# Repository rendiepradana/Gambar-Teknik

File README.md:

# Gambar-Teknik

Hello i'am Rendie Pradana

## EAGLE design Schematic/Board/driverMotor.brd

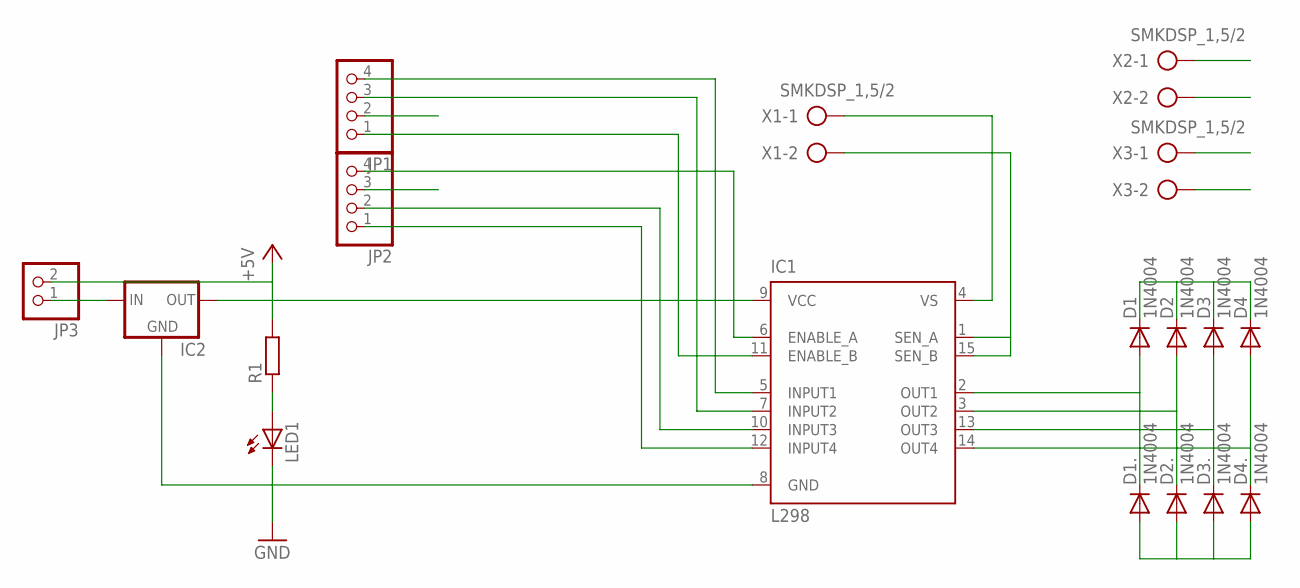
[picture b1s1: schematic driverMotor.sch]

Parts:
D1, D1., D2, D2., D3, D3., D4, D4.: 1N4004; DO41-10
IC1: L298; MULTIWATT-15
IC2: 78MXXS
JP1, JP2: PINHD-1X4; 1X04
JP3: PINHD-1X2; 1X02
LED1: LED5MM
R1: R-EU_0411/12; 0411/12
X1, X2, X3: SMKDSP_1,5/2

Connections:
+5V: IC1.9 (VCC), IC2.OUT, JP1.2, JP3.2, R1.2
ENABLE_A: IC1.6 (ENABLE_A), JP2.4
ENABLE_B: IC1.11 (ENABLE_B), JP1.1
GND: D1..A, D2..A, D3..A, D4..A, IC1.1 (SEN_A), IC1.8 (GND), IC1.15 (SEN_B), IC2.GND, JP2.3, LED1.K (C), X1.2
INPUT1: IC1.5 (INPUT1), JP1.4
INPUT2: IC1.7 (INPUT2), JP1.3
INPUT3: IC1.10 (INPUT3), JP2.2
INPUT4: IC1.12 (INPUT4), JP2.1
LED: LED1.A, R1.1
MOTOR1_1: D1.A, D1..C, IC1.2 (OUT1), X2.1
MOTOR1_2: D2.A, D2..C, IC1.3 (OUT2), X2.2
MOTOR2_1: D3.A, D3..C, IC1.13 (OUT3), X3.1
MOTOR2_2: D4.A, D4..C, IC1.14 (OUT4), X3.2
VS: D1.C, D2.C, D3.C, D4.C, IC1.4 (VS), IC2.IN, JP3.1, X1.1

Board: 2 copper layers, 18 parts (0 on the bottom side), 14 nets, no tracks yet.

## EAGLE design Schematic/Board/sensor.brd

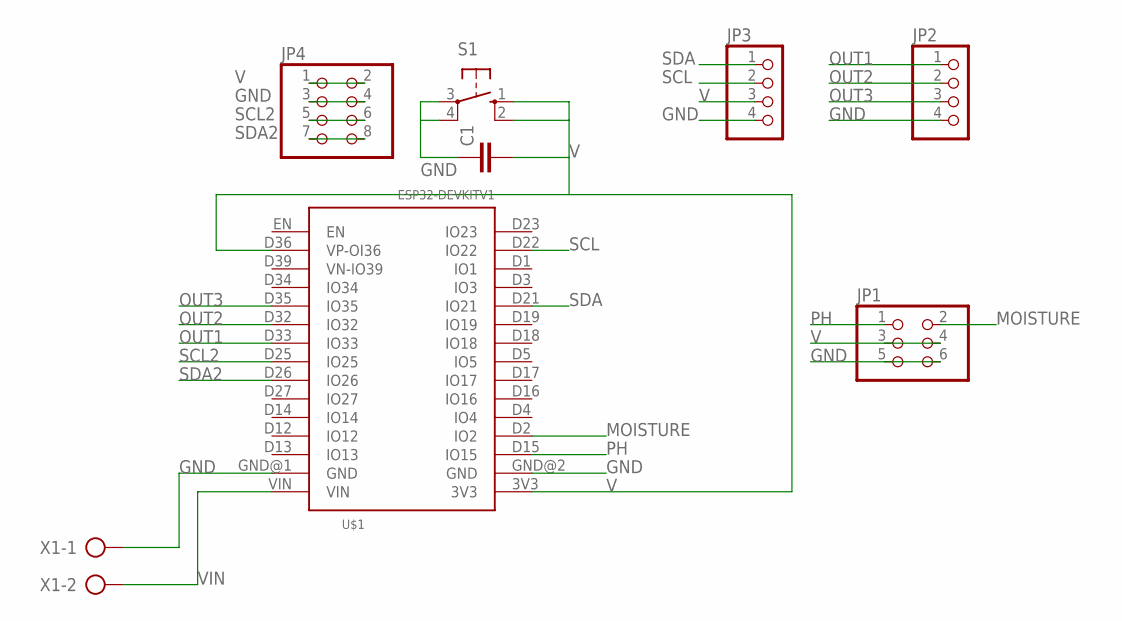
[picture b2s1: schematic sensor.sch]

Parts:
C1: C-EU050-030X075; C050-030X075
JP1: PINHD-2X3; 2X03
JP2, JP3: PINHD-1X4; 1X04
JP4: PINHD-2X4; 2X04
S1: 10-XX; B3F-10XX
U$1: ESP32DEVKITV1; ESP32-DEVKITV1
X1: AK300/2

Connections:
GND: C1.1, JP1.5, JP1.6, JP2.4, JP3.4, JP4.3, JP4.4, S1.3, S1.4 (P1), U$1.GND@1 (GND), U$1.GND@2 (GND), X1.1
MOISTURE: JP1.2, U$1.D2 (IO2)
OUT1: JP2.1, U$1.D33 (IO33)
OUT2: JP2.2, U$1.D32 (IO32)
OUT3: JP2.3, U$1.D35 (IO35)
PH: JP1.1, U$1.D15 (IO15)
SCL: JP3.2, U$1.D22 (IO22)
SCL2: JP4.5, JP4.6, U$1.D25 (IO25)
SDA: JP3.1, U$1.D21 (IO21)
SDA2: JP4.7, JP4.8, U$1.D26 (IO26)
V: C1.2, JP1.3, JP1.4, JP3.3, JP4.1, JP4.2, S1.1 (S), S1.2 (S1), U$1.3V3, U$1.D36 (VP-OI36)
VIN: U$1.VIN, X1.2

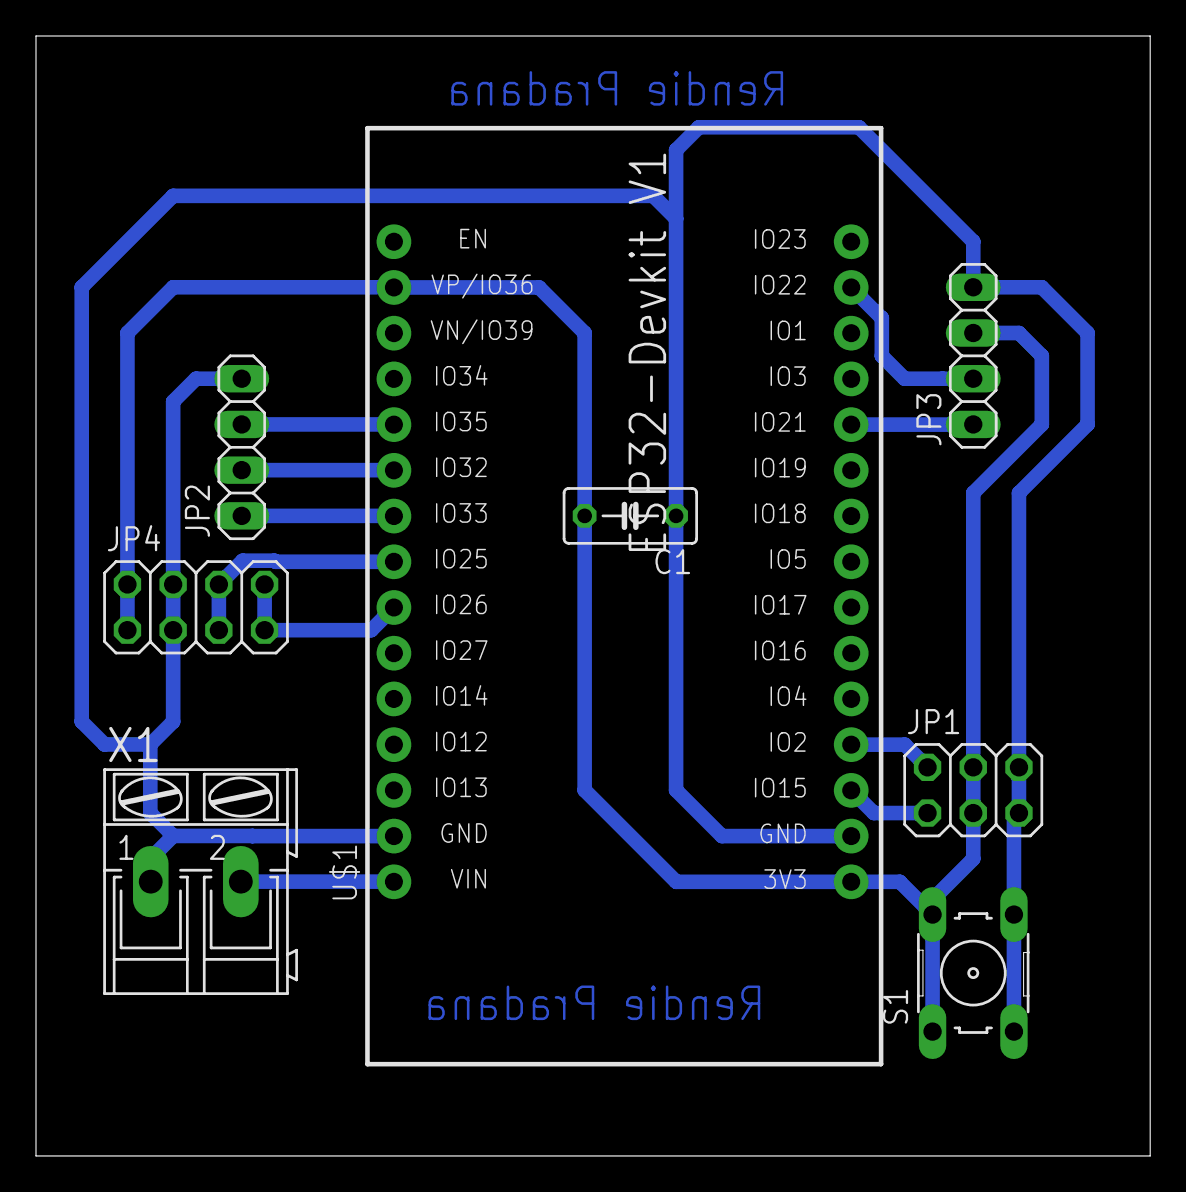
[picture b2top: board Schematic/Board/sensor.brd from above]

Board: 2 copper layers, 61.9 x 62.2 mm, 8 parts (0 on the bottom side), 12 nets.

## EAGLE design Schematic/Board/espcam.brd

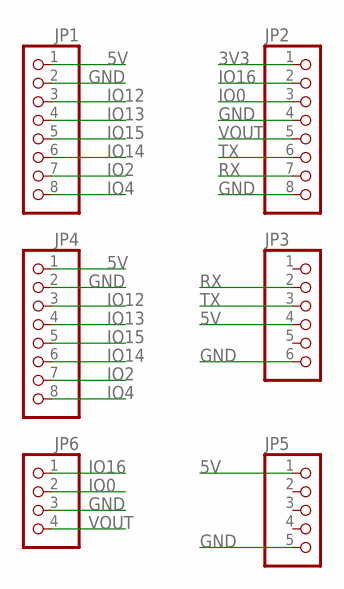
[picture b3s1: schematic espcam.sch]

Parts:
JP1, JP2, JP4: PINHD-1X8; 1X08
JP3: PINHD-1X6; 1X06
JP5: PINHD-1X5; 1X05
JP6: PINHD-1X4; 1X04

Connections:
3V3: JP2.1
5V: JP1.1, JP3.4, JP4.1, JP5.1
GND: JP1.2, JP2.4, JP2.8, JP3.6, JP4.2, JP5.5, JP6.3
IO0: JP2.3, JP6.2
IO2: JP1.7, JP4.7
IO4: JP1.8, JP4.8
IO12: JP1.3, JP4.3
IO13: JP1.4, JP4.4
IO14: JP1.6, JP4.6
IO15: JP1.5, JP4.5
IO16: JP2.2, JP6.1
RX: JP2.7, JP3.2
TX: JP2.6, JP3.3
VOUT: JP2.5, JP6.4

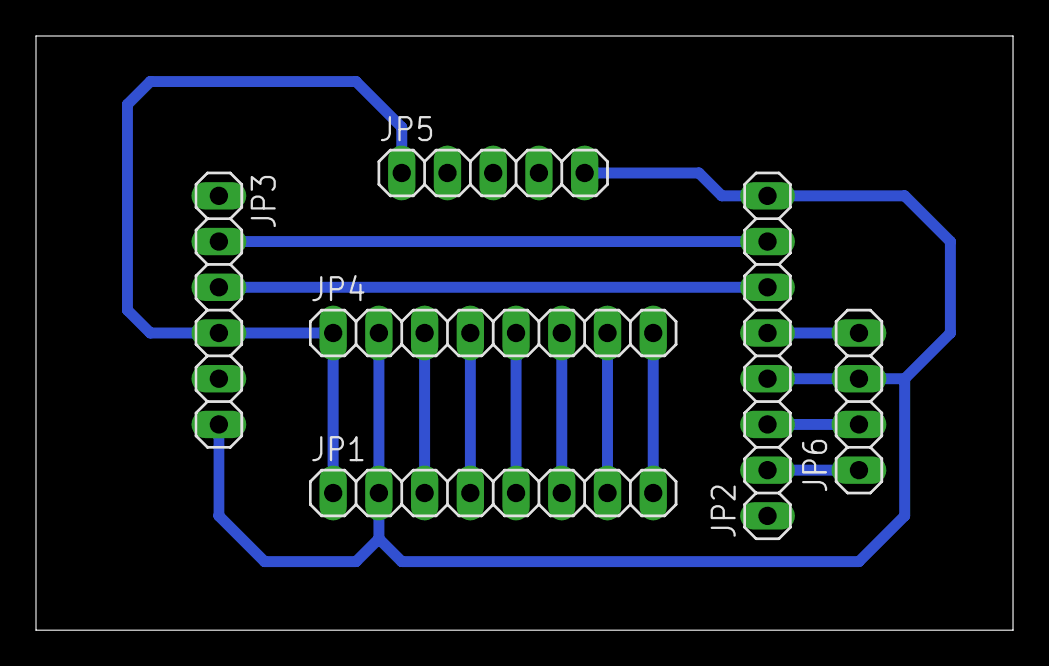
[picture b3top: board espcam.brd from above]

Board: 2 copper layers, 54.3 x 33.0 mm, 6 parts (0 on the bottom side), 13 nets.

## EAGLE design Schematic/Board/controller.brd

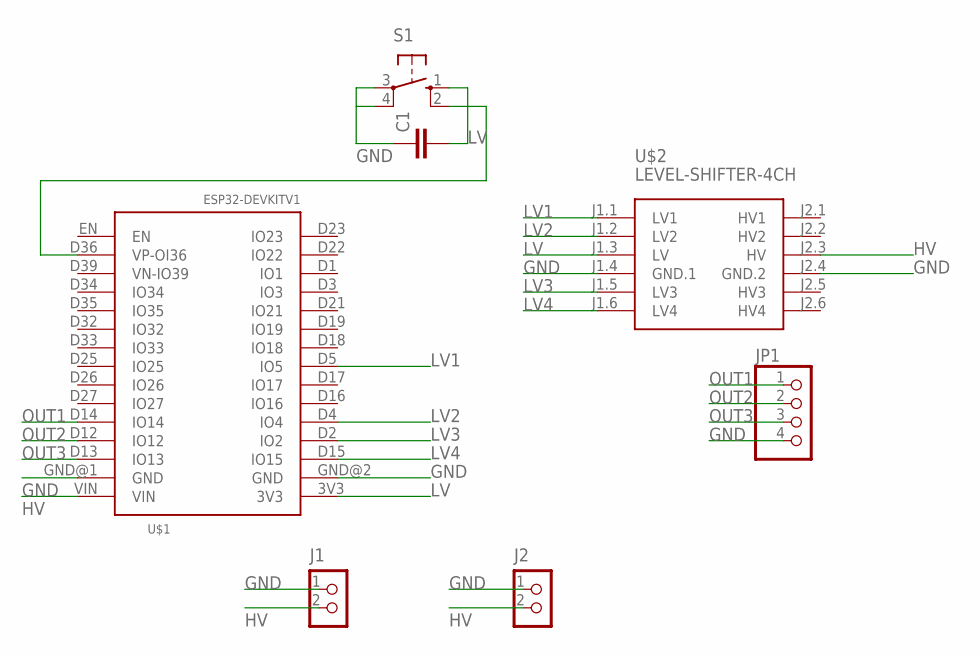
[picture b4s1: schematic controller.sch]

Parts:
C1: C-EU025-025X050; C025-025X050
J1, J2: CON_TERMINAL_BLOCK_02-5MM; TERMINAL_BLOCK_2P_5
JP1: PINHD-1X4; 1X04
S1: 10-XX; B3F-10XX
U$1: ESP32DEVKITV1; ESP32-DEVKITV1
U$2: LEVEL-SHIFTER-4CH

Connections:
GND: C1.1, J1.1, J2.1, JP1.4, S1.3, S1.4 (P1), U$1.GND@1 (GND), U$1.GND@2 (GND), U$2.J1.4 (GND.1), U$2.J2.4 (GND.2)
HV: J1.2, J2.2, U$1.VIN, U$2.J2.3 (HV)
LV: C1.2, S1.1 (S), S1.2 (S1), U$1.3V3, U$1.D36 (VP-OI36), U$2.J1.3 (LV)
LV1: U$1.D5 (IO5), U$2.J1.1 (LV1)
LV2: U$1.D4 (IO4), U$2.J1.2 (LV2)
LV3: U$1.D2 (IO2), U$2.J1.5 (LV3)
LV4: U$1.D15 (IO15), U$2.J1.6 (LV4)
OUT1: JP1.1, U$1.D14 (IO14)
OUT2: JP1.2, U$1.D12 (IO12)
OUT3: JP1.3, U$1.D13 (IO13)

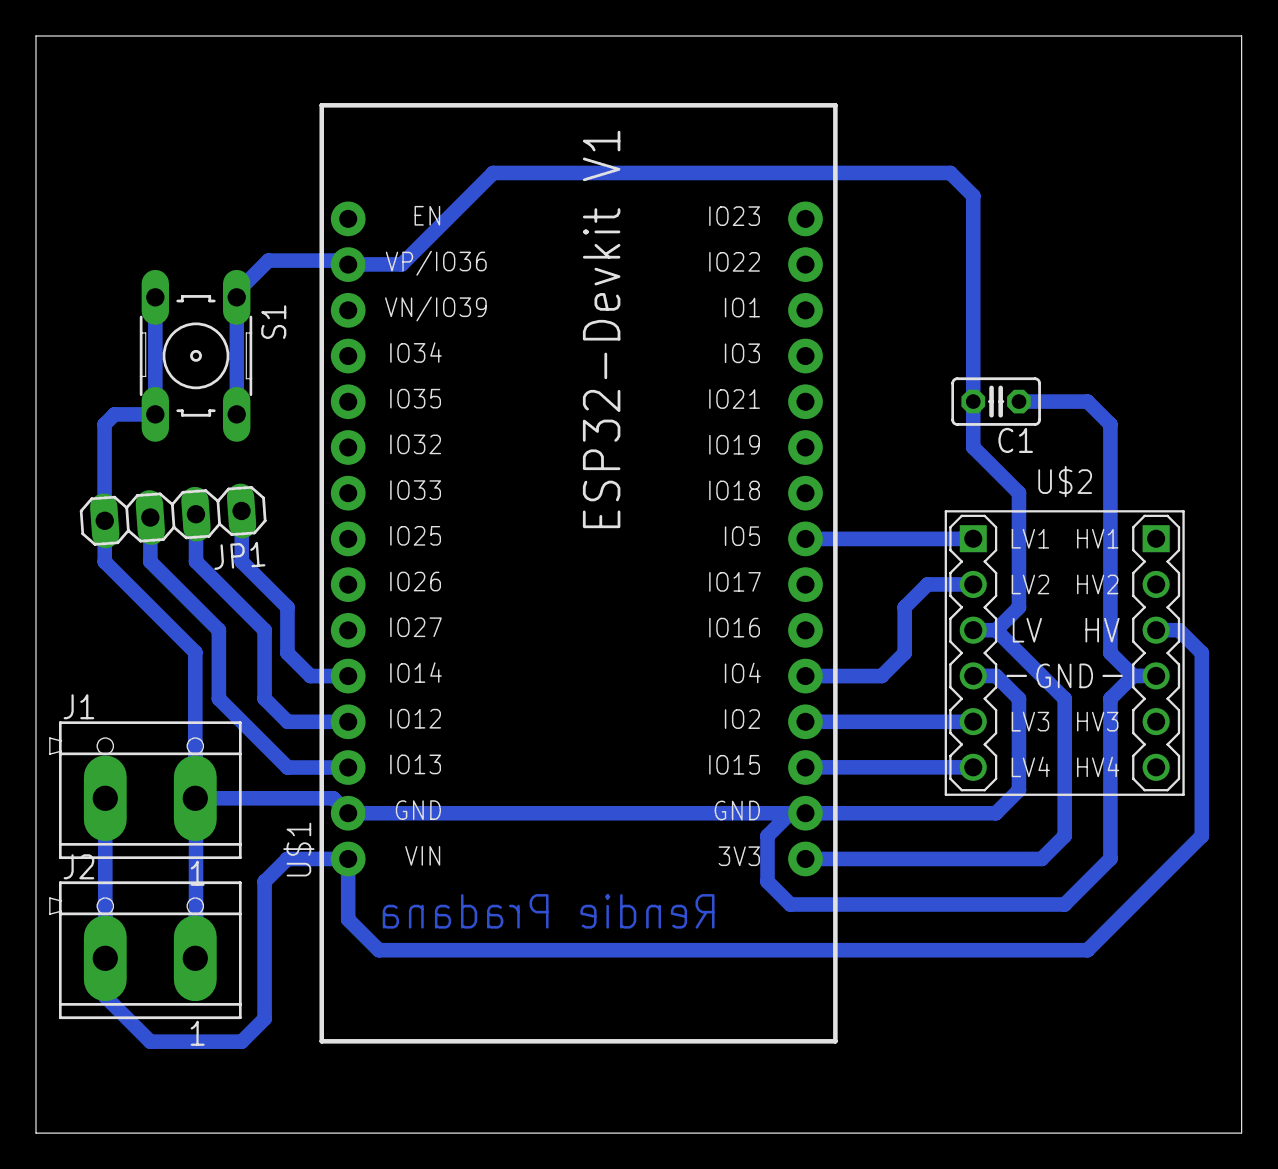
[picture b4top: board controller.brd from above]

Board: 2 copper layers, 67.0 x 61.0 mm, 7 parts (0 on the bottom side), 10 nets.

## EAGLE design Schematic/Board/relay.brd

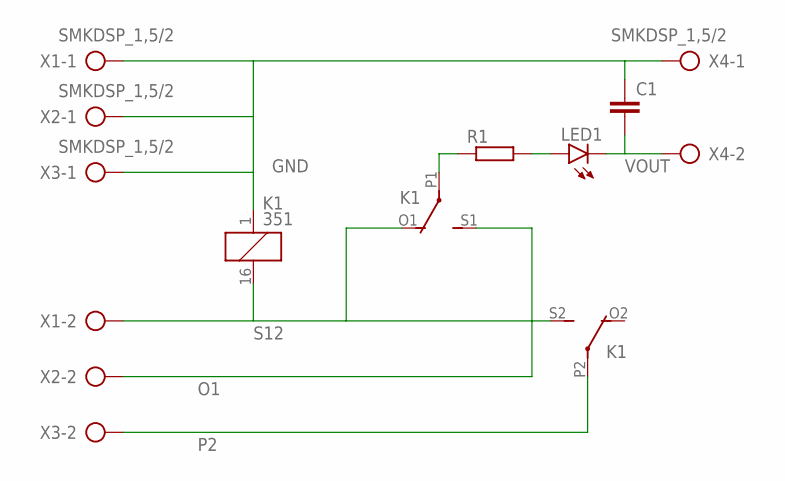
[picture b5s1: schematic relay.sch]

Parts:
C1: C-EU025-025X050; C025-025X050
K1: 351
LED1: LED3MM
R1: R-EU_0207/10; 0207/10
X1, X2, X3, X4: SMKDSP_1,5/2

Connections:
GND: C1.1, K1.1, X1.1, X2.1, X3.1, X4.1
unnamed: K1.P1, R1.1
unnamed: LED1.A, R1.2
O1: K1.S1 (S), X2.2
P2: K1.P2, X3.2
S12: K1.16 (2), K1.O1 (O), K1.S2 (S), X1.2
VOUT: C1.2, LED1.K (C), X4.2

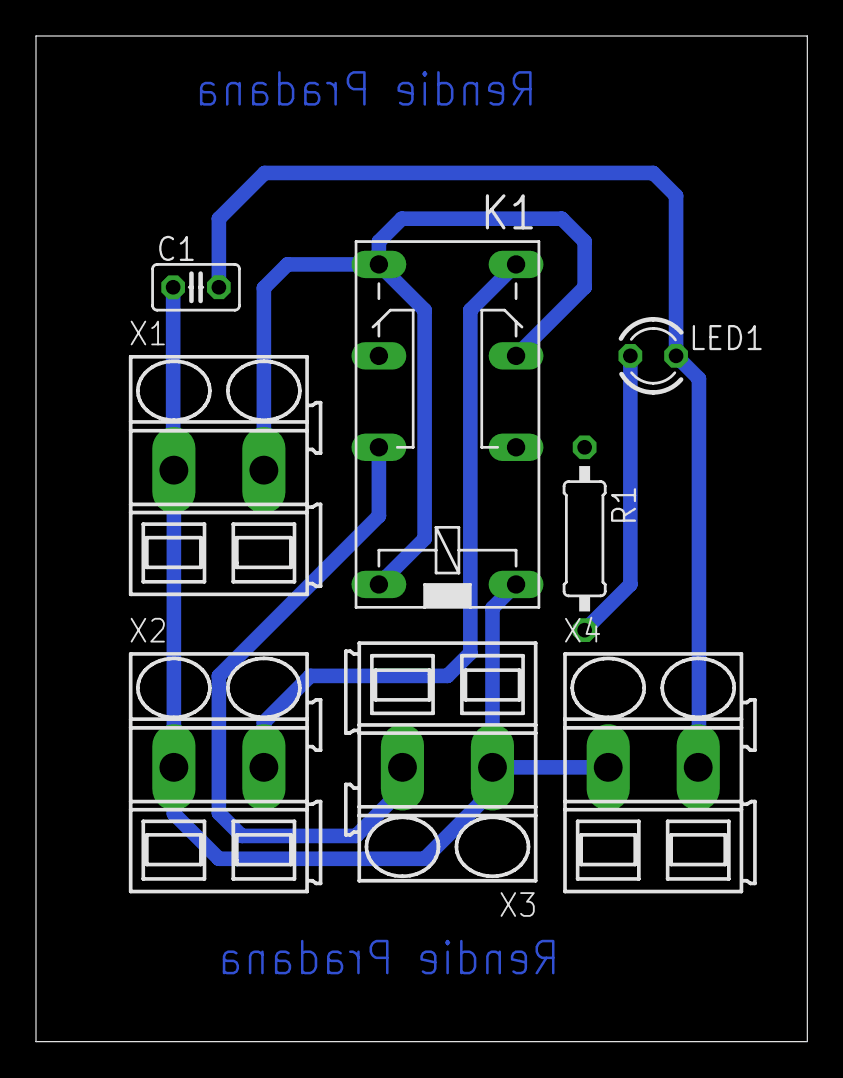
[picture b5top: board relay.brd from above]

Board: 2 copper layers, 42.8 x 55.9 mm, 8 parts (0 on the bottom side), 7 nets.

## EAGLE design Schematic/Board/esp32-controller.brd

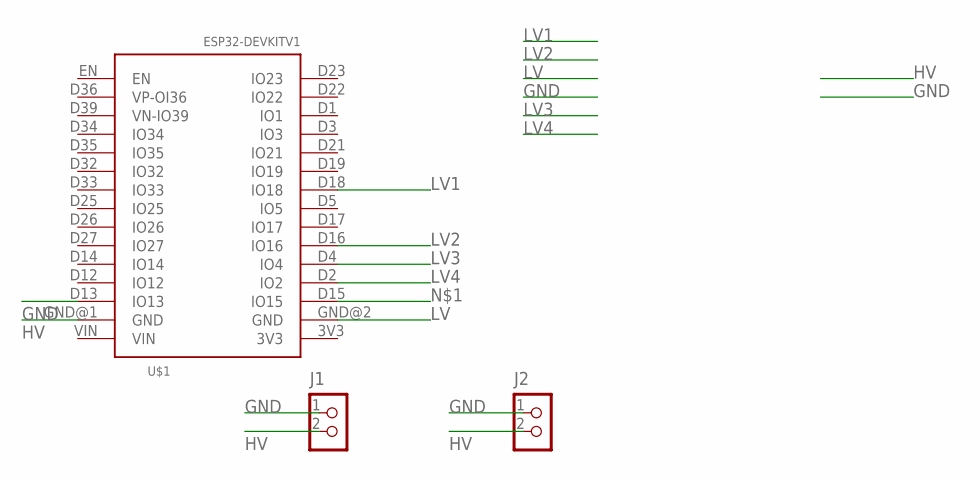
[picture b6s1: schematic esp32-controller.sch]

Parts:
J1, J2: CON_TERMINAL_BLOCK_02-5MM; TERMINAL_BLOCK_2P_5
U$1: ESP32DEVKITV1; ESP32-DEVKITV1

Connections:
GND: J1.1, J2.1, U$1.D13 (IO13)
HV: J1.2, J2.2, U$1.GND@1 (GND)
LV: U$1.GND@2 (GND)
LV1: U$1.D18 (IO18)
LV2: U$1.D16 (IO16)
LV3: U$1.D4 (IO4)
LV4: U$1.D2 (IO2)

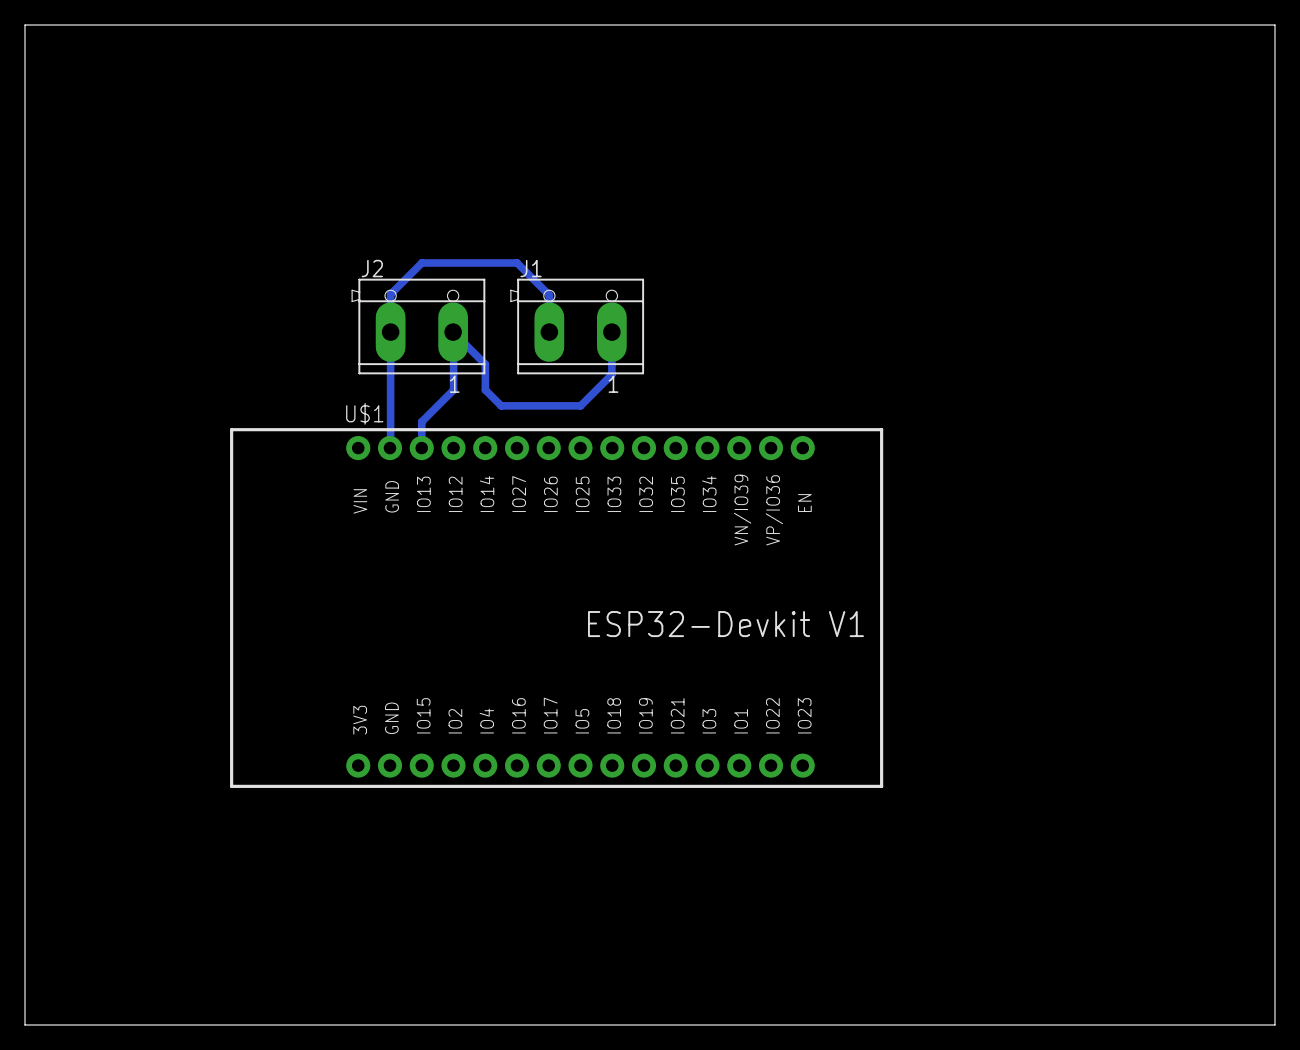
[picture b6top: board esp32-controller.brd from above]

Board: 2 copper layers, 100.0 x 80.0 mm, 3 parts (0 on the bottom side), 2 nets.

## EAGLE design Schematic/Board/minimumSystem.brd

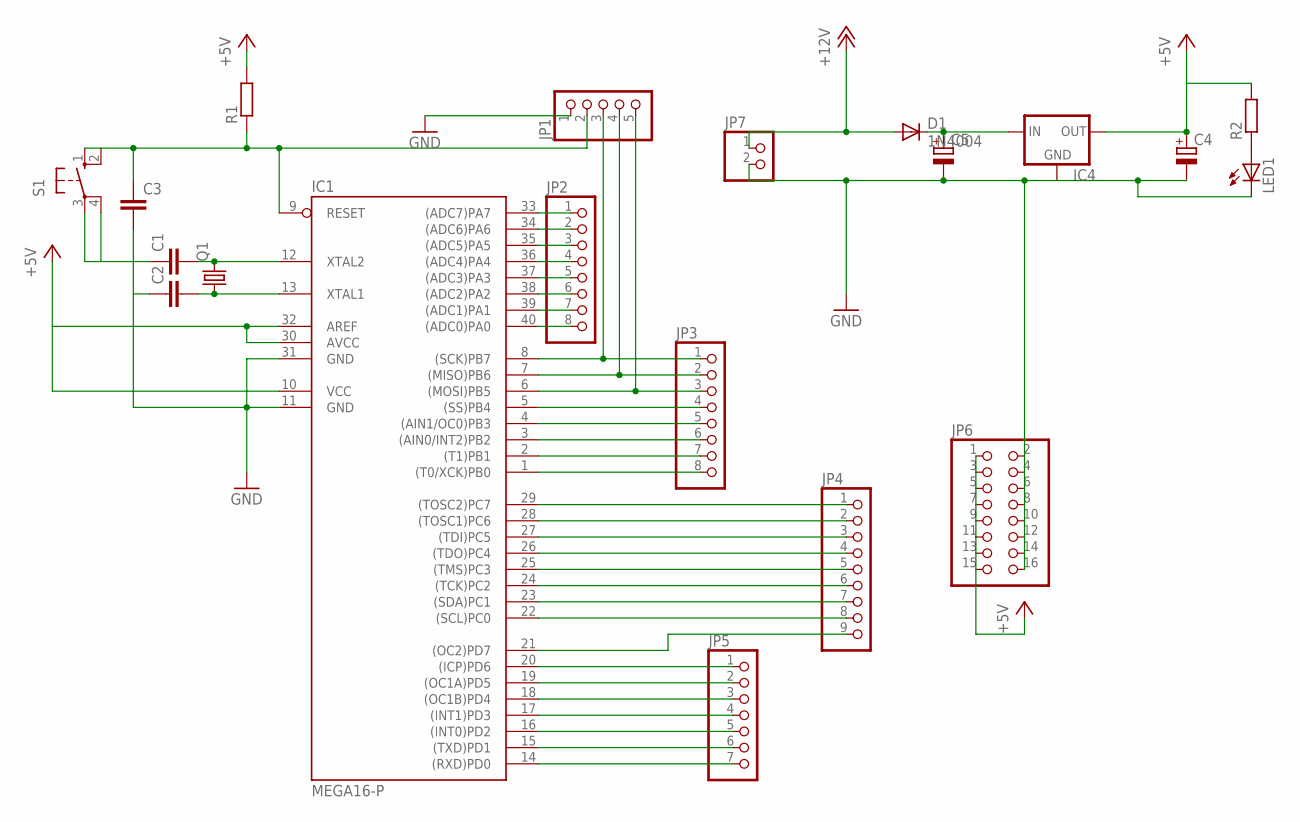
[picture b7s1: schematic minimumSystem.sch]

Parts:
C1, C2: C-EU025-024X044; C025-024X044
C3: C-EU050-025X075; C050-025X075
C4, C5: CPOL-EUE2.5-5; E2,5-5
D1: 1N4004; DO41-10
IC1: MEGA16-P; DIL40
IC4: 78XXS
JP1: PINHD-1X5; 1X05
JP2, JP3: PINHD-1X8; 1X08
JP4: PINHD-1X9; 1X09
JP5: PINHD-1X7; 1X07
JP6: PINHD-2X8; 2X08
JP7: PINHD-1X2; 1X02
LED1: LED5MM
Q1: CRYSTALHC49U-V; HC49U-V
R1, R2: R-EU_0204/7; 0204/7
S1: 10-XX; B3F-10XX

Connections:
+5V: C4.+, IC1.10 (VCC), IC1.30 (AVCC), IC1.32 (AREF), IC4.OUT, JP6.1, JP6.3, JP6.5, JP6.7, JP6.9, JP6.11, JP6.13, JP6.15, R1.2, R2.2
+12V: D1.A, JP7.1
C0: IC1.22 ((SCL)PC0), JP4.8
C1: IC1.23 ((SDA)PC1), JP4.7
C2: IC1.24 ((TCK)PC2), JP4.6
C3: IC1.25 ((TMS)PC3), JP4.5
D7: IC1.14 ((RXD)PD0), JP5.7
GND: C1.1, C2.1, C3.2, C4.-, C5.-, IC1.11 (GND), IC1.31 (GND), IC4.GND, JP1.1, JP6.2, JP6.4, JP6.6, JP6.8, JP6.10, JP6.12, JP6.14, JP6.16, JP7.2, LED1.K (C), S1.3, S1.4 (P1)
unnamed: IC1.33 ((ADC7)PA7), JP2.1
unnamed: IC1.34 ((ADC6)PA6), JP2.2
unnamed: IC1.35 ((ADC5)PA5), JP2.3
unnamed: IC1.36 ((ADC4)PA4), JP2.4
unnamed: IC1.37 ((ADC3)PA3), JP2.5
unnamed: IC1.38 ((ADC2)PA2), JP2.6
unnamed: IC1.39 ((ADC1)PA1), JP2.7
unnamed: IC1.40 ((ADC0)PA0), JP2.8
unnamed: IC1.29 ((TOSC2)PC7), JP4.1
unnamed: IC1.28 ((TOSC1)PC6), JP4.2
unnamed: IC1.27 ((TDI)PC5), JP4.3
unnamed: IC1.5 ((SS)PB4), JP3.4
unnamed: IC1.20 ((ICP)PD6), JP5.1
unnamed: IC1.19 ((OC1A)PD5), JP5.2
unnamed: IC1.26 ((TDO)PC4), JP4.4
unnamed: IC1.6 ((MOSI)PB5), JP1.5, JP3.3
unnamed: IC1.4 ((AIN1/OC0)PB3), JP3.5
unnamed: IC1.3 ((AIN0/INT2)PB2), JP3.6
unnamed: IC1.2 ((T1)PB1), JP3.7
unnamed: IC1.1 ((T0/XCK)PB0), JP3.8
unnamed: C5.+, D1.C, IC4.IN
unnamed: IC1.15 ((TXD)PD1), JP5.6
unnamed: IC1.16 ((INT0)PD2), JP5.5
unnamed: IC1.17 ((INT1)PD3), JP5.4
unnamed: C3.1, IC1.9 (RESET), JP1.2, R1.1, S1.1 (S), S1.2 (S1)
unnamed: IC1.18 ((OC1B)PD4), JP5.3
unnamed: C1.2, IC1.12 (XTAL2), Q1.2
unnamed: C2.2, IC1.13 (XTAL1), Q1.1
unnamed: LED1.A, R2.1
unnamed: IC1.8 ((SCK)PB7), JP1.3, JP3.1
unnamed: IC1.7 ((MISO)PB6), JP1.4, JP3.2
RS: IC1.21 ((OC2)PD7), JP4.9

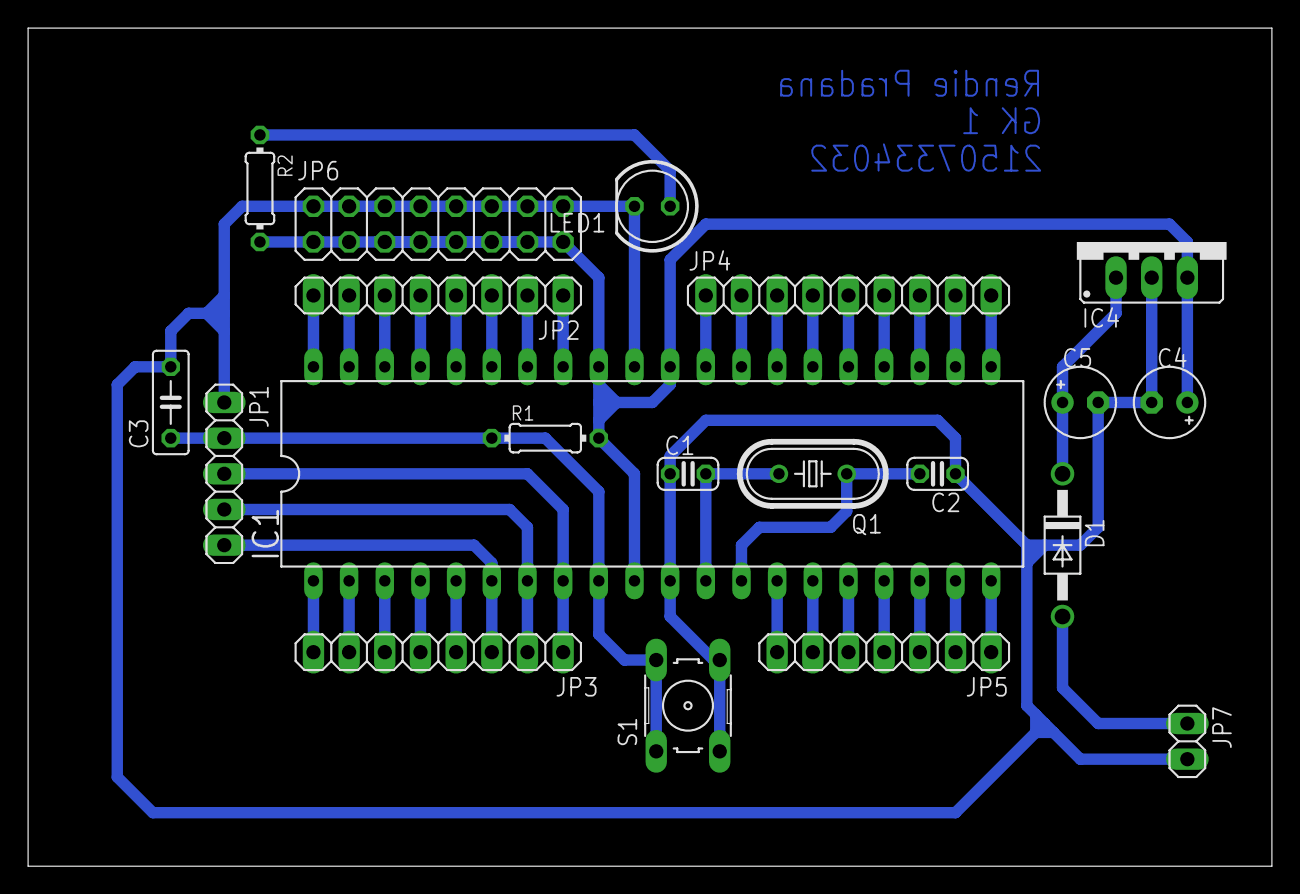
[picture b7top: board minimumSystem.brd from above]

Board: 2 copper layers, 88.6 x 59.7 mm, 20 parts (0 on the bottom side), 40 nets.

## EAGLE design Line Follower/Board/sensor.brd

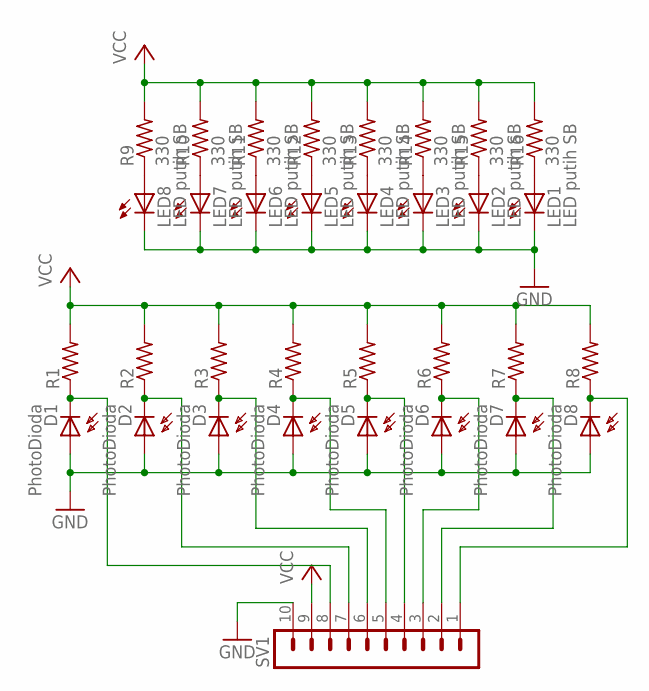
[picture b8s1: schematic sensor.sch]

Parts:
D1, D2, D3, D4, D5, D6, D7, D8: PhotoDioda; SFH225
LED1, LED2, LED3, LED4, LED5, LED6, LED7, LED8: LED putih SB; LED5MM
R1, R2, R3, R4, R5, R6, R7, R8: R-US_0207/10; 0207/10
R9, R10, R11, R12, R13, R14, R15, R16: 330; 0207/10
SV1: MA10-1

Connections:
GND: D1.A, D2.A, D3.A, D4.A, D5.A, D6.A, D7.A, D8.A, LED1.K (C), LED2.K (C), LED3.K (C), LED4.K (C), LED5.K (C), LED6.K (C), LED7.K (C), LED8.K (C), SV1.10
unnamed: LED7.A, R10.1
unnamed: D7.K (C), R7.1, SV1.2
unnamed: D8.K (C), R8.1, SV1.1
unnamed: D1.K (C), R1.1, SV1.8
unnamed: D2.K (C), R2.1, SV1.7
unnamed: D3.K (C), R3.1, SV1.6
unnamed: D5.K (C), R5.1, SV1.4
unnamed: D4.K (C), R4.1, SV1.5
unnamed: D6.K (C), R6.1, SV1.3
unnamed: LED6.A, R11.1
unnamed: LED5.A, R12.1
unnamed: LED4.A, R13.1
unnamed: LED3.A, R14.1
unnamed: LED2.A, R15.1
unnamed: LED1.A, R16.1
unnamed: LED8.A, R9.1
VCC: R1.2, R2.2, R3.2, R4.2, R5.2, R6.2, R7.2, R8.2, R9.2, R10.2, R11.2, R12.2, R13.2, R14.2, R15.2, R16.2, SV1.9

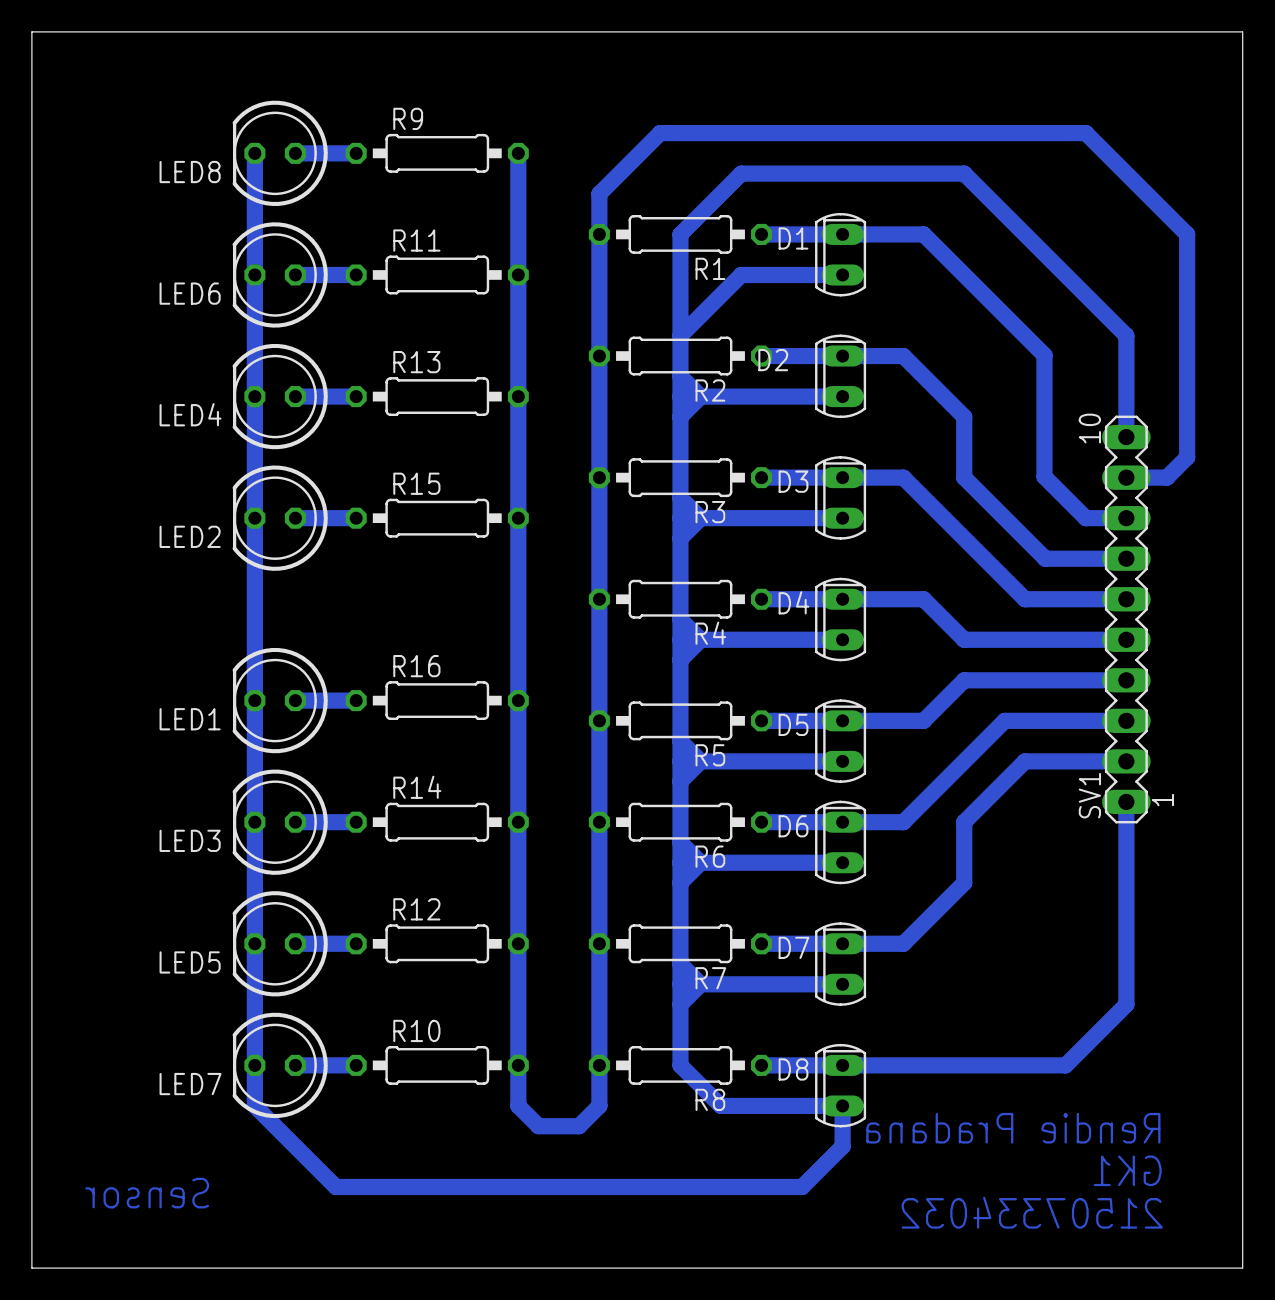
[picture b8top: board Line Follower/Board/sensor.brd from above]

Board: 2 copper layers, 75.9 x 77.5 mm, 33 parts (0 on the bottom side), 18 nets.

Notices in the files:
parts and their libraries:
diy-model: Released under the Creative Commons Attribution 4.0 International License: http://creativecommons.org/licenses/by/4.0
